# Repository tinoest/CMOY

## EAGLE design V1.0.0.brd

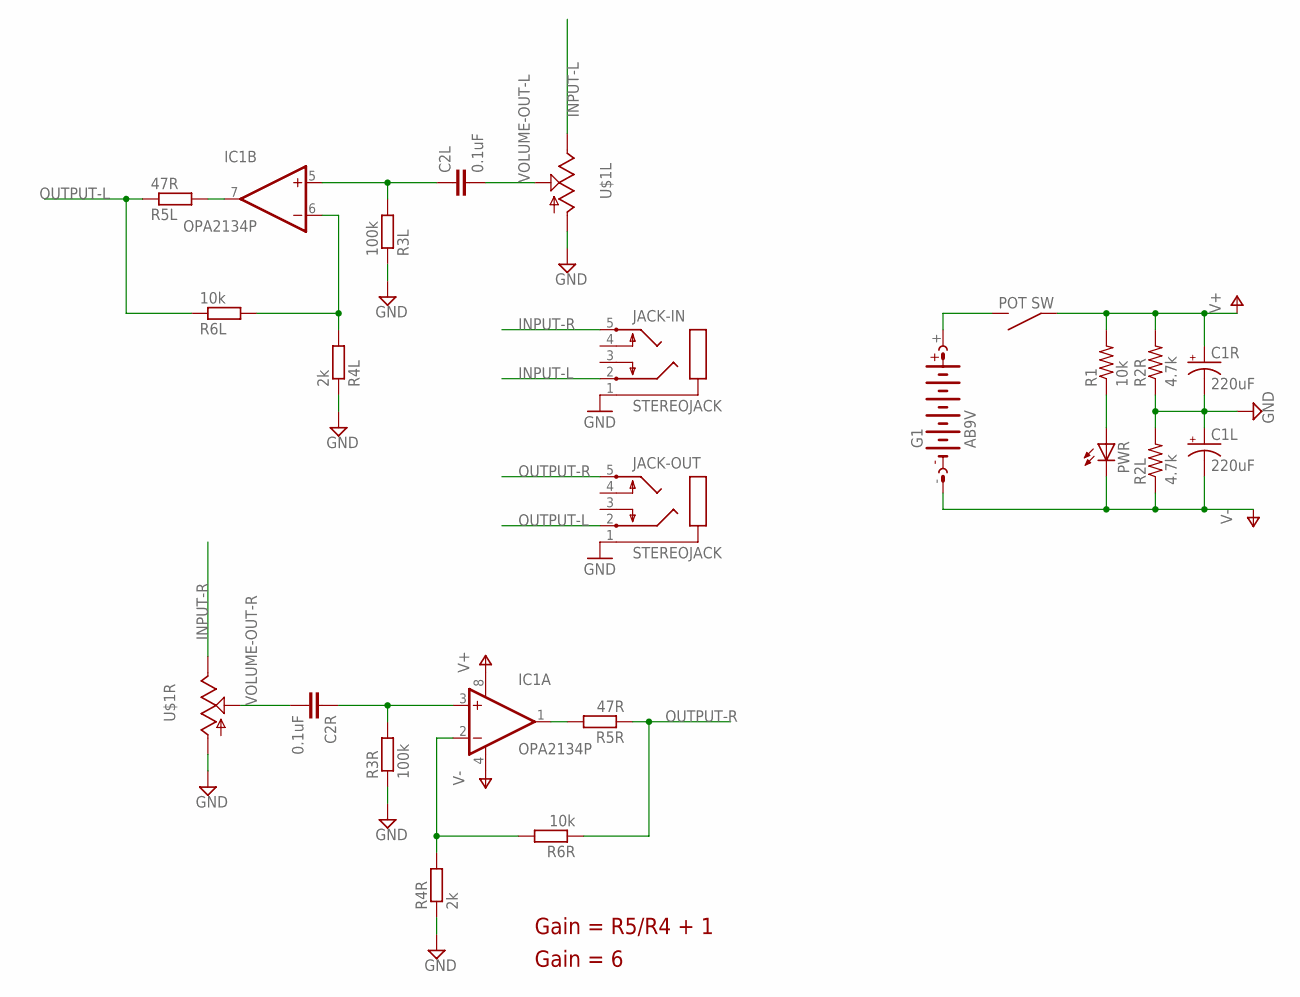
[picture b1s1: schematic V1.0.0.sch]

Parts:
C1L, C1R: 220uF; CPOL-RADIAL-6.3MM
C2L, C2R: 0.1uF; C5B5
G1: AB9V
IC1: OPA2134P; DIL-8
JACK-IN: STEREOJACK; STX3100
JACK-OUT: STEREOJACK; STX3100
PWR: LED-3MM-MINUS; LED3MM-MINUS
R1: 10k; 1/6W-RES-OUTLINE
R2L, R2R: 4.7k; 1/6W-RES-OUTLINE
R3L, R3R: 100k; 0207/2V
R4L, R4R: 2k; 0207/2V
R5L, R5R: 47R; 0207/2V
R6L, R6R: 10k; 0207/2V
U$1: ALPS_RK0971221Z05; ALPS_RK0971221Z0X

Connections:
GND: C1L.1 (+), C1R.2 (-), JACK-IN.1, JACK-OUT.1, R2L.2, R2R.1, R3L.1, R3R.1, R4L.1, R4R.1, U$1.G1 (1), U$1.G2 (1)
INPUT-L: JACK-IN.2, U$1.I1 (3)
INPUT-R: JACK-IN.5, U$1.I2 (3)
L+: C2L.1, IC1.5 (+IN), R3L.2
L-: IC1.6 (-IN), R4L.2, R6L.2
unnamed: PWR.A, R1.1
unnamed: G1.+, U$1.S2
OP-L: IC1.7 (OUT), R5L.2
OP-R: IC1.1 (OUT), R5R.2
OUTPUT-L: JACK-OUT.2, R5L.1, R6L.1
OUTPUT-R: JACK-OUT.5, R5R.1, R6R.1
R+: C2R.1, IC1.3 (+IN), R3R.2
R-: IC1.2 (-IN), R4R.2, R6R.2
V+: C1R.1 (+), IC1.8 (V+), R1.2, R2R.2, U$1.S1
V-: C1L.2 (-), G1.-, IC1.4 (V-), PWR.K (C), R2L.1
VOLUME-OUT-L: C2L.2, U$1.O1 (2)
VOLUME-OUT-R: C2R.2, U$1.O2 (2)

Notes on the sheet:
Gain = R5/R4 + 1
Gain = 6

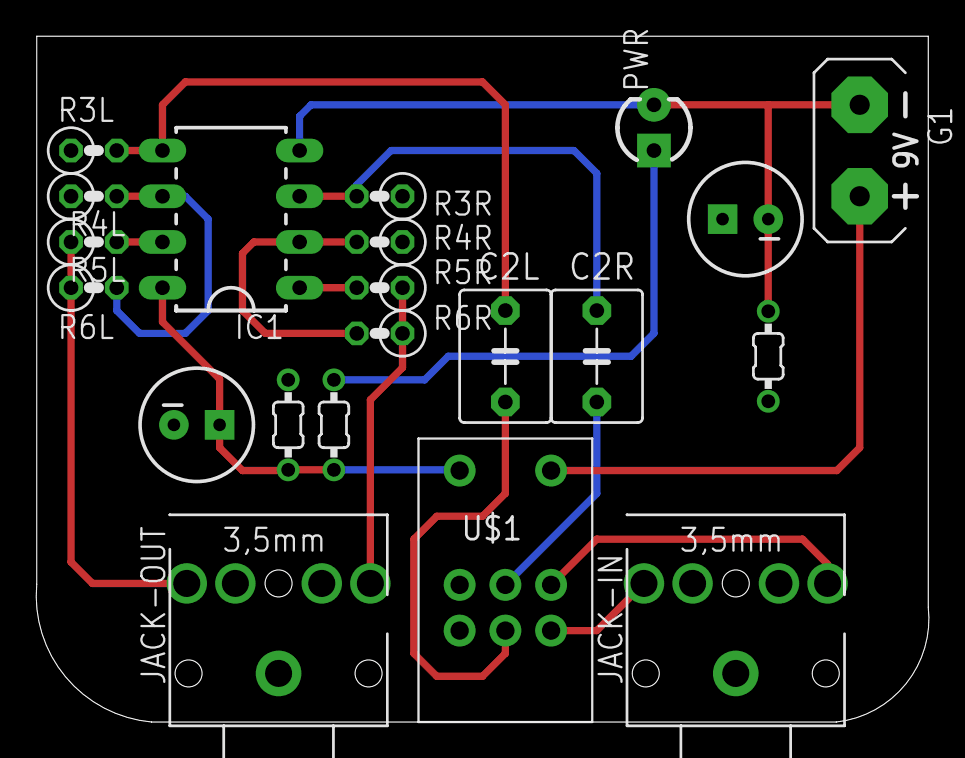
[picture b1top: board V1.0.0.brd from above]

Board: 2 copper layers, 49.6 x 38.1 mm, 21 parts (0 on the bottom side), 17 nets.

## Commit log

2017-03-31 Adding old CMOY data files created in Eagle
    CMOY Amplifier Circuit and Board
2017-03-31 Created kicad PCB files
2017-03-31 First conversion to kicad
2017-03-31 Moved V1.0.0 to kicad
2017-03-31 Modified slightly to fix some ERC issues
2017-03-31 Moved to indvidual directories
2017-03-31 Modified PCB and Schematic so they were in sync
2017-03-31 Removed unrequired files
2017-03-31 Started to include libraries and sort out names to link to PCB
2017-03-31 Corrected Schematic errors
2017-03-31 Added cache.lib
2017-04-01 Corrected conversion errors
2017-04-01 Moved eaglecad files into eagle directory
